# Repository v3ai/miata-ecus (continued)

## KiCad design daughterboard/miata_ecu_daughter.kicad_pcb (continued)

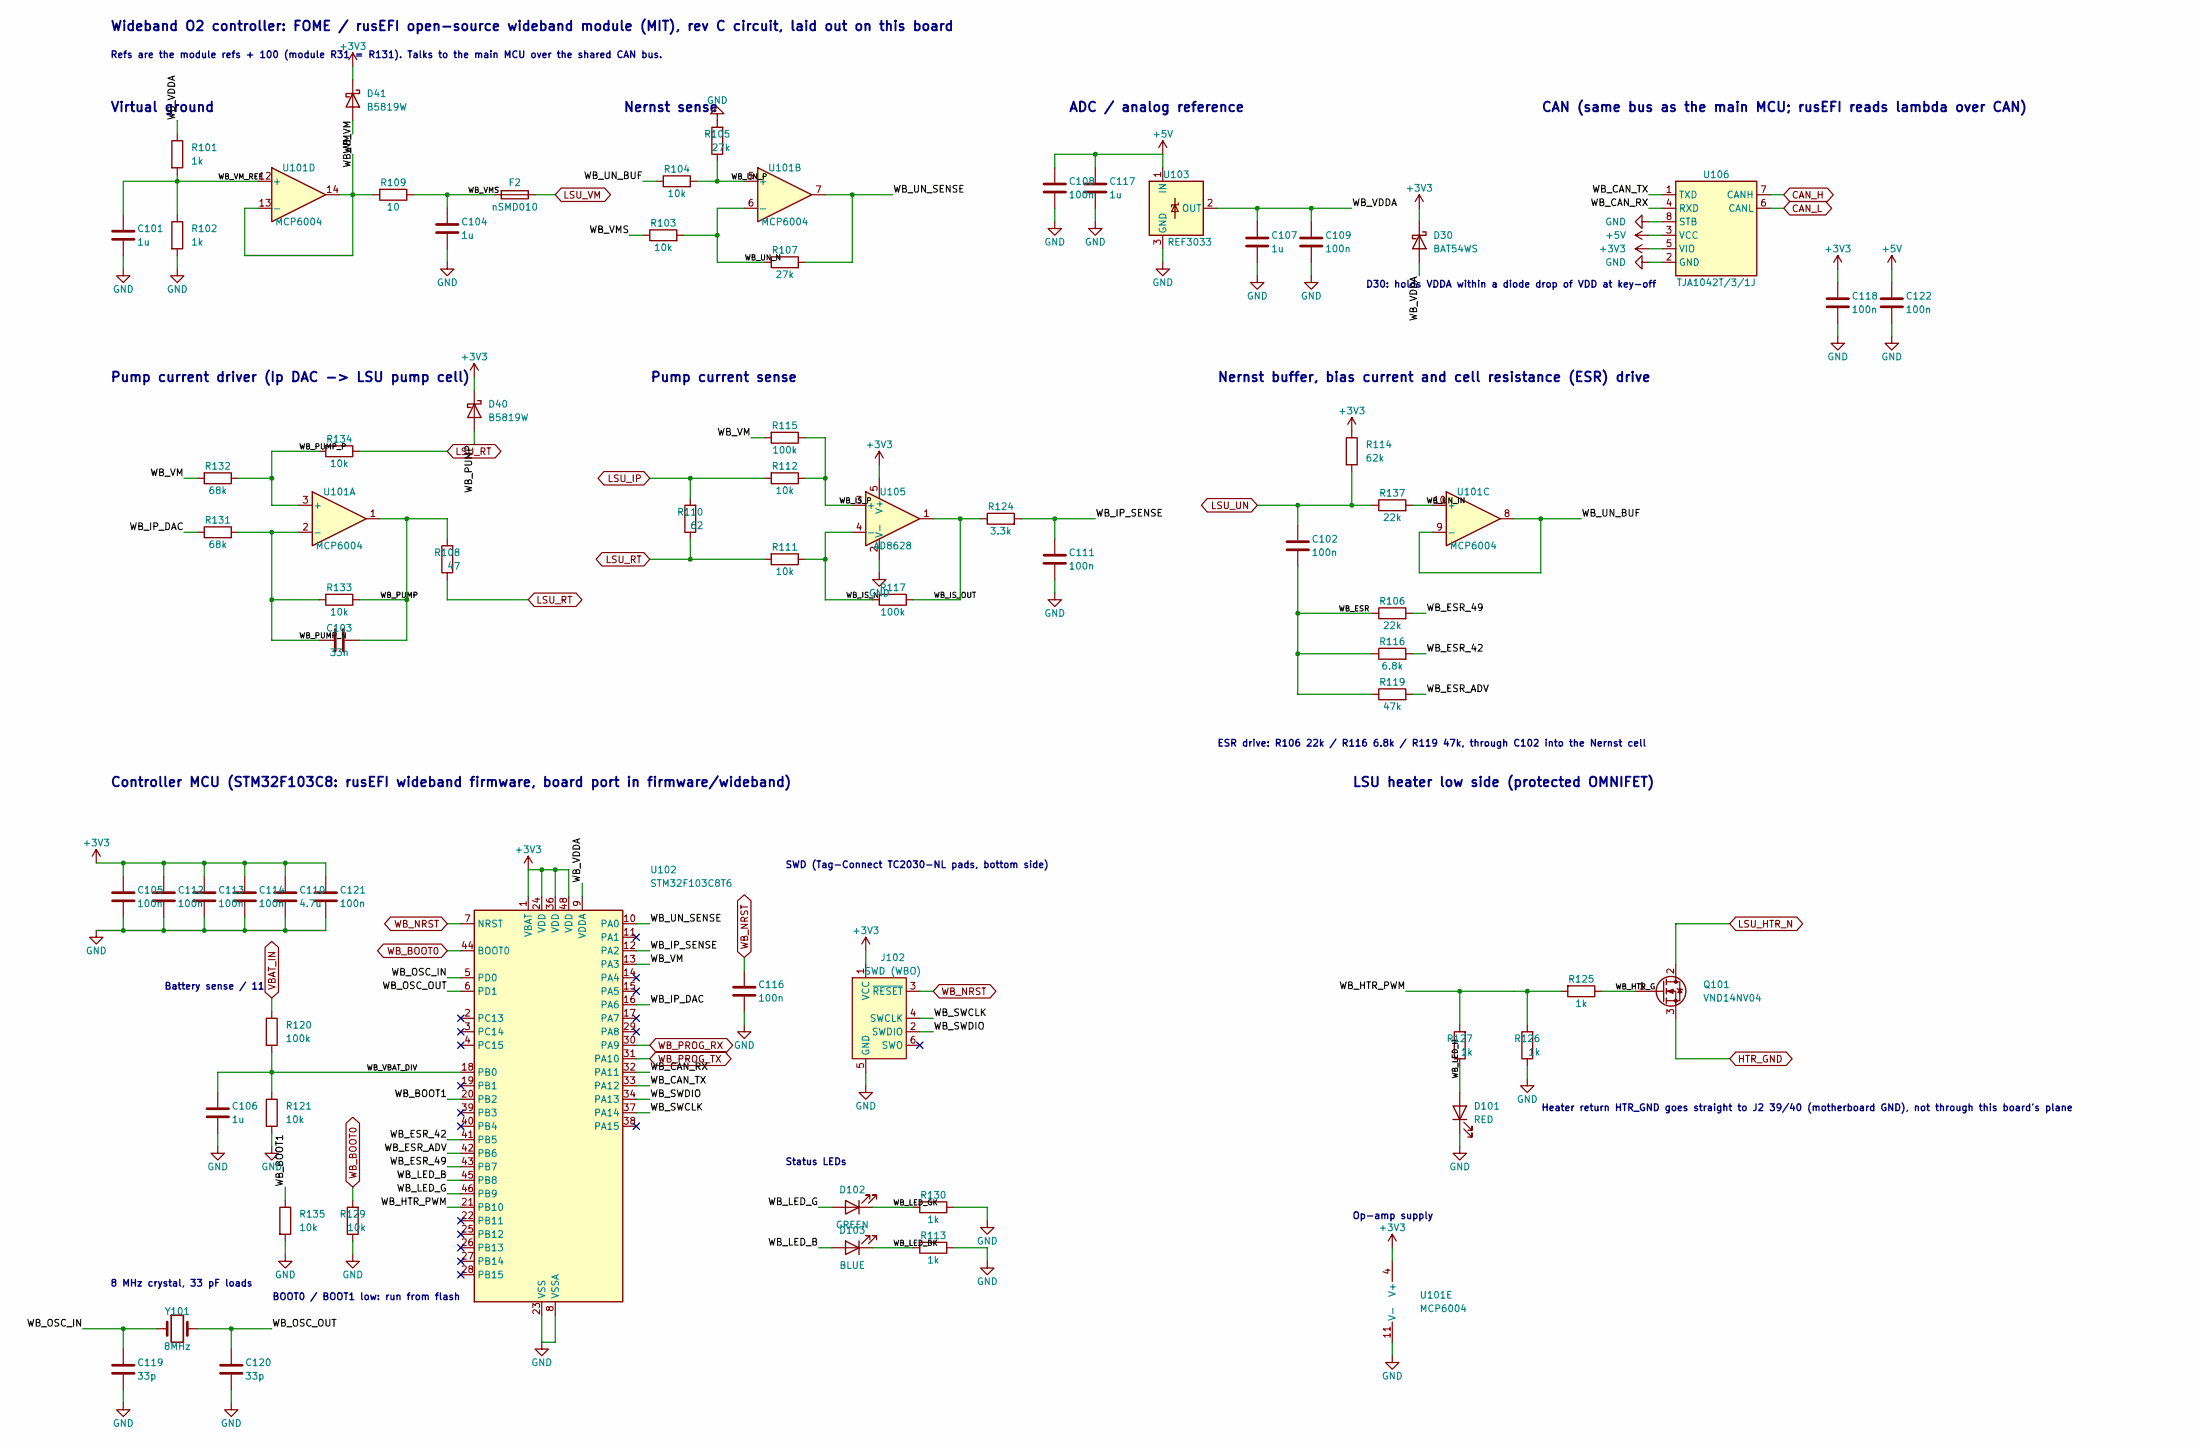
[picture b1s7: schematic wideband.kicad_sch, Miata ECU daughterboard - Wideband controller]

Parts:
C101, C104, C106, C107, C117: 1u; C_0402_1005Metric; LCSC C52923
C102, C105, C108, C109, C111, C112, C113, C114, C116, C118, C121, C122: 100n; C_0402_1005Metric; LCSC C1525
C103: 33n; C_0402_1005Metric; LCSC C106862
C110: 4.7u; C_0603_1608Metric; LCSC C19666
C119, C120: 33p; C_0402_1005Metric; LCSC C1562
D30: BAT54WS; D_SOD-323; LCSC C124205
D40, D41: B5819W; D_SOD-123; LCSC C8598
D101: RED; LED_0603_1608Metric; LCSC C2286
D102: GREEN; LED_0603_1608Metric; LCSC C12624
D103: BLUE; LED_0603_1608Metric; LCSC C2288
F2: nSMD010; Fuse_1206_3216Metric; LCSC C70065
J102: SWD (WBO); Tag-Connect_TC2030-IDC-NL_2x03_P1.27mm_Vertical
Q101: VND14NV04; TO-252-2; LCSC C2649436
R101, R102, R113, R125, R126, R127, R130: 1k; R_0402_1005Metric; LCSC C11702
R103, R104, R111, R112, R121, R129, R133, R134, R135: 10k; R_0402_1005Metric; LCSC C25744
R105, R107: 27k; R_0402_1005Metric; LCSC C25771
R106, R137: 22k; R_0402_1005Metric; LCSC C25768
R108: 47; R_1206_3216Metric; LCSC C17969
R109: 10; R_1206_3216Metric; LCSC C17903
R110: 62; R_1206_3216Metric; LCSC C17971
R114: 62k; R_0603_1608Metric; LCSC C23221
R115, R117, R120: 100k; R_0402_1005Metric; LCSC C25741
R116: 6.8k; R_0402_1005Metric; LCSC C25917
R119: 47k; R_0402_1005Metric; LCSC C25792
R124: 3.3k; R_0402_1005Metric; LCSC C25890
R131, R132: 68k; R_0402_1005Metric; LCSC C36871
U101: MCP6004; TSSOP-14_4.4x5mm_P0.65mm; LCSC C50282
U102: STM32F103C8T6; LQFP-48_7x7mm_P0.5mm; LCSC C8734
U103: REF3033; SOT-23; LCSC C36658
U105: AD8628; SOT-23-5; LCSC C29309
U106: TJA1042T/3/1J; SOIC-8_3.9x4.9mm_P1.27mm; LCSC C132227
Y101: 8MHz; Crystal_SMD_5032-2Pin_5.0x3.2mm; LCSC C115962

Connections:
+3V3: C105.1, C110.1, C112.1, C113.1, C114.1, C118.1, C121.1, D30.1 (K), D40.1 (K), D41.1 (K), J102.1 (VCC), R114.1, U101.4 (V+), U102.1 (VBAT), U102.24 (VDD), U102.36 (VDD), U102.48 (VDD), U105.5 (V+), U106.5 (VIO); also elsewhere on the board
+5V: C108.1, C117.1, C122.1, U103.1 (IN), U106.3 (VCC); also elsewhere on the board
/Wideband controller/WB_BOOT1: R135.1, U102.20 (PB2)
/Wideband controller/WB_CAN_RX: U102.32 (PA11), U106.4 (RXD)
/Wideband controller/WB_CAN_TX: U102.33 (PA12), U106.1 (TXD)
/Wideband controller/WB_ESR: C102.2, R106.1, R116.1, R119.1
/Wideband controller/WB_ESR_42: R116.2, U102.41 (PB5)
/Wideband controller/WB_ESR_49: R106.2, U102.43 (PB7)
/Wideband controller/WB_ESR_ADV: R119.2, U102.42 (PB6)
/Wideband controller/WB_HTR_G: Q101.1 (G), R125.1
/Wideband controller/WB_HTR_PWM: R125.2, R126.2, R127.2, U102.21 (PB10)
/Wideband controller/WB_IP_DAC: R131.1, U102.16 (PA6)
/Wideband controller/WB_IP_SENSE: C111.1, R124.2, U102.12 (PA2)
/Wideband controller/WB_IS_N: R111.1, R117.2, U105.4 (-)
/Wideband controller/WB_IS_OUT: R117.1, R124.1, U105.1
/Wideband controller/WB_IS_P: R112.1, R115.1, U105.3 (+)
/Wideband controller/WB_LED_B: D103.2 (A), U102.45 (PB8)
/Wideband controller/WB_LED_BK: D103.1 (K), R113.2
/Wideband controller/WB_LED_G: D102.2 (A), U102.46 (PB9)
/Wideband controller/WB_LED_GK: D102.1 (K), R130.2
/Wideband controller/WB_LED_H: D101.2 (A), R127.1
/Wideband controller/WB_OSC_IN: C119.1, U102.5 (PD0), Y101.1
/Wideband controller/WB_OSC_OUT: C120.1, U102.6 (PD1), Y101.2
/Wideband controller/WB_PUMP: C103.1, D40.2 (A), R108.2, R133.1, U101.1
/Wideband controller/WB_PUMP_N: C103.2, R131.2, R133.2, U101.2 (-)
/Wideband controller/WB_PUMP_P: R132.1, R134.2, U101.3 (+)
/Wideband controller/WB_SWCLK: J102.4 (SWCLK), U102.37 (PA14)
/Wideband controller/WB_SWDIO: J102.2 (SWDIO), U102.34 (PA13)
/Wideband controller/WB_UN_BUF: R104.1, U101.8, U101.9 (-)
/Wideband controller/WB_UN_IN: R137.2, U101.10 (+)
/Wideband controller/WB_UN_N: R103.2, R107.1, U101.6 (-)
/Wideband controller/WB_UN_P: R104.2, R105.1, U101.5 (+)
/Wideband controller/WB_UN_SENSE: R107.2, U101.7, U102.10 (PA0)
/Wideband controller/WB_VBAT_DIV: C106.1, R120.2, R121.1, U102.18 (PB0)
/Wideband controller/WB_VDDA: C107.1, C109.1, D30.2 (A), R101.1, U102.9 (VDDA), U103.2 (OUT)
/Wideband controller/WB_VM: D41.2 (A), R109.2, R115.2, R132.2, U101.13 (-), U101.14, U102.13 (PA3)
/Wideband controller/WB_VMS: C104.1, F2.2, R103.1, R109.1
/Wideband controller/WB_VM_REF: C101.1, R101.2, R102.1, U101.12 (+)
CAN_H: U106.7 (CANH); also elsewhere on the board
CAN_L: U106.6 (CANL); also elsewhere on the board
GND: C101.2, C104.2, C105.2, C106.2, C107.2, C108.2, C109.2, C110.2, C111.2, C112.2, C113.2, C114.2, C116.2, C117.2, C118.2, C119.2, C120.2, C121.2, C122.2, D101.1 (K), J102.5 (GND), R102.2, R105.2, R113.1, R121.2, R126.1, R129.1, R130.1, R135.2, U101.11 (V-), U102.8 (VSSA), U102.23 (VSS), U102.35 (VSS), U102.47 (VSS), U103.3 (GND), U105.2 (V-), U106.2 (GND), U106.8 (STB); also elsewhere on the board
HTR_GND: Q101.3 (S); also elsewhere on the board
LSU_HTR_N: Q101.2 (D); also elsewhere on the board
LSU_IP: R110.2, R112.2; also elsewhere on the board
LSU_RT: R108.1, R110.1, R111.2, R134.1; also elsewhere on the board
LSU_UN: C102.1, R114.2, R137.1; also elsewhere on the board
LSU_VM: F2.1; also elsewhere on the board
VBAT_IN: R120.1; also elsewhere on the board
WB_BOOT0: R129.2, U102.44 (BOOT0); also elsewhere on the board
WB_NRST: C116.1, J102.3 (~RESET), U102.7 (NRST); also elsewhere on the board
WB_PROG_RX: U102.30 (PA9); also elsewhere on the board
WB_PROG_TX: U102.31 (PA10); also elsewhere on the board

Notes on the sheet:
Wideband O2 controller: FOME / rusEFI open-source wideband module (MIT), rev C circuit, laid out on this board
Refs are the module refs + 100 (module R31 = R131). Talks to the main MCU over the shared CAN bus.
Virtual ground
Nernst sense
ADC / analog reference
D30: holds VDDA within a diode drop of VDD at key-off
CAN (same bus as the main MCU; rusEFI reads lambda over CAN)
Pump current driver (Ip DAC -> LSU pump cell)
Pump current sense
Nernst buffer, bias current and cell resistance (ESR) drive
ESR drive: R106 22k / R116 6.8k / R119 47k, through C102 into the Nernst cell
Controller MCU (STM32F103C8: rusEFI wideband firmware, board port in firmware/wideband)
BOOT0 / BOOT1 low: run from flash
Battery sense / 11
8 MHz crystal, 33 pF loads
Status LEDs
SWD (Tag-Connect TC2030-NL pads, bottom side)
LSU heater low side (protected OMNIFET)
Heater return HTR_GND goes straight to J2 39/40 (motherboard GND), not through this board's plane
Op-amp supply

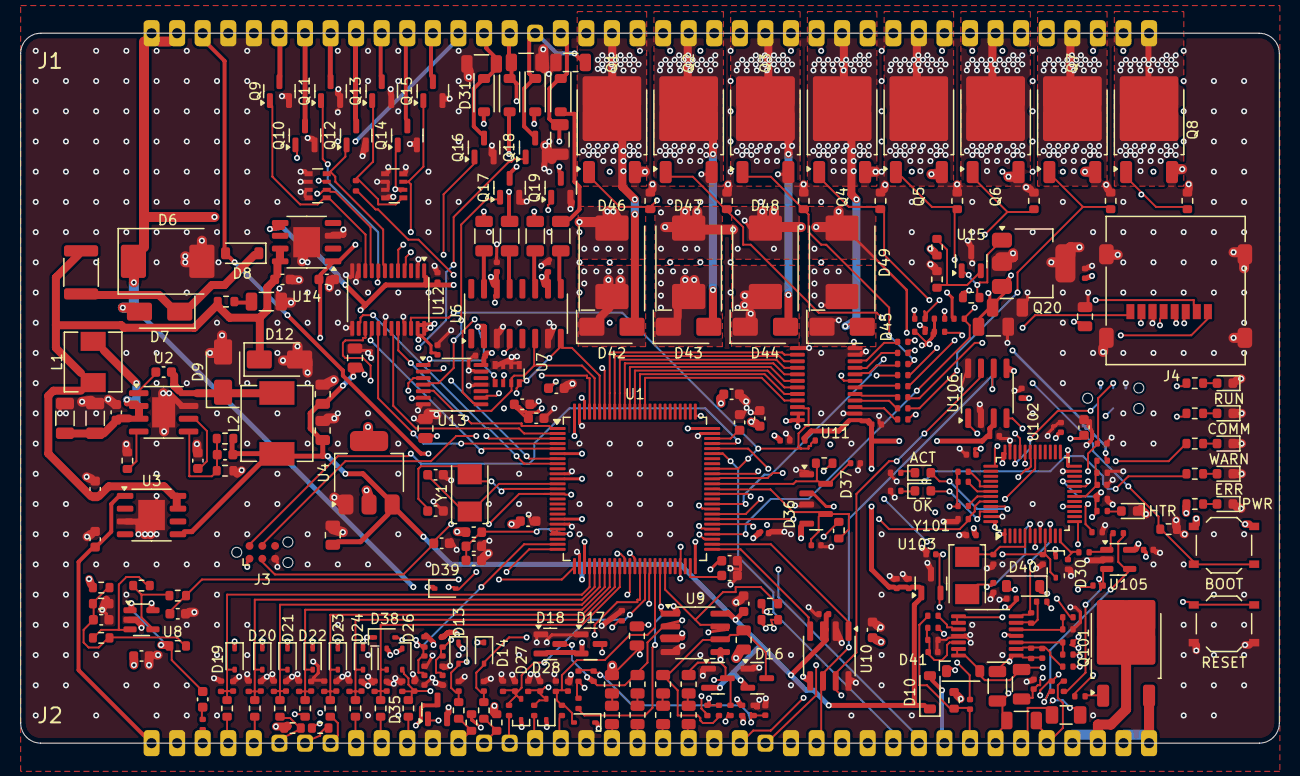
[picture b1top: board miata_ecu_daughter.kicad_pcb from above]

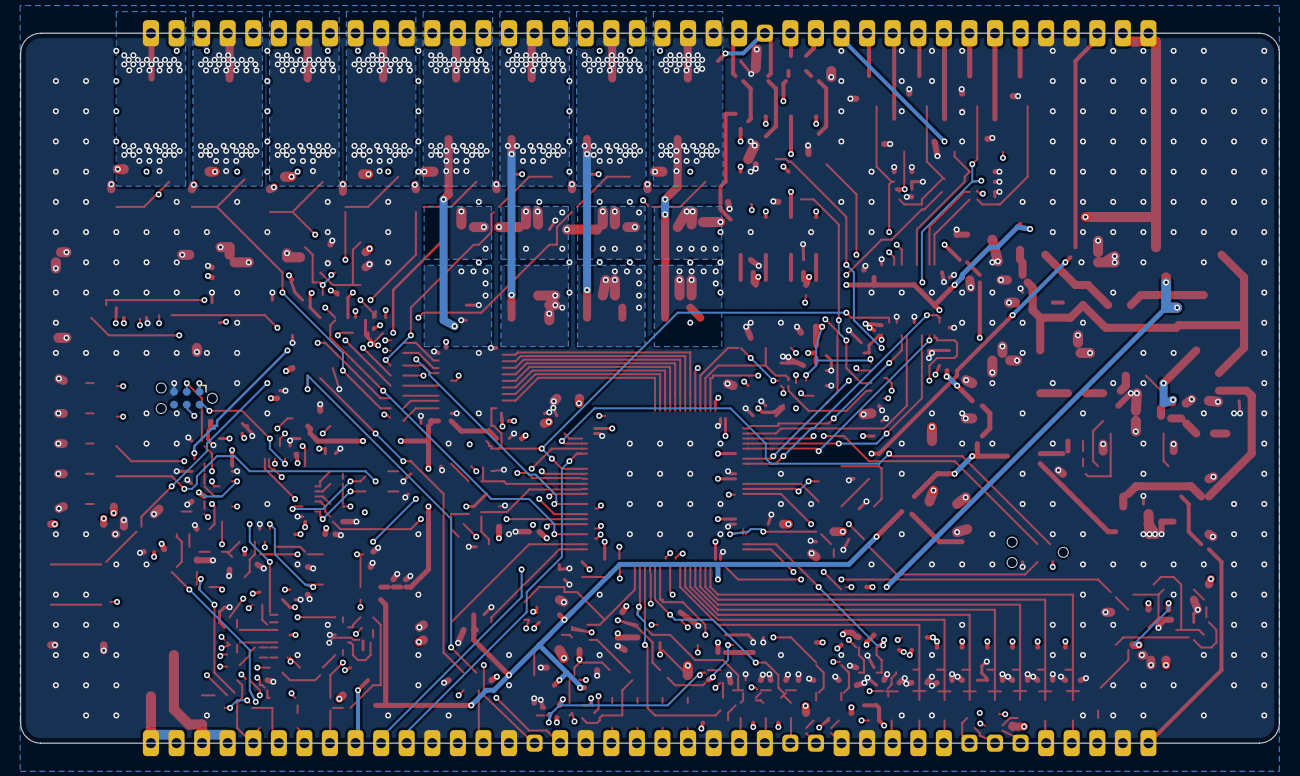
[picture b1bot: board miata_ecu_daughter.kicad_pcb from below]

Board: 6 copper layers, 125.0 x 70.5 mm, 334 parts (3 on the bottom side), 230 nets.

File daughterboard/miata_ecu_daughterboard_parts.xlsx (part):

Group | Qty | Value | Description | Designators | Footprint | LCSC # | JLC type | Notes | Manufacturer | MPN
MCU & support
MCU & support | 7 | 100n |  | C1, C2, C3, C5, C6, C12, C15 | C_0603_1608Metric | C14663 | Basic |  | YAGEO | CC0603KRX7R9BB104
MCU & support | 1 | 100n |  | C4 | C_0402_1005Metric | C1525 | Basic |  | Samsung Electro-Mechanics | CL05B104KO5NNNC
MCU & support | 1 | 10k |  | R1 | R_0603_1608Metric | C25804 | Basic |  | UNI-ROYAL(Uniroyal Elec) | 0603WAF1002T5E
MCU & support | 1 | 1u |  | C11 | C_0603_1608Metric | C15849 | Basic |  | Samsung Electro-Mechanics | CL10A105KB8NNNC
MCU & support | 2 | 2.2u |  | C9, C10 | C_0603_1608Metric | C23630 | Basic |  | Samsung Electro-Mechanics | CL10A225KO8NNNC
MCU & support | 2 | 33p |  | C13, C14 | C_0603_1608Metric | C1663 | Extended |  | Samsung Electro-Mechanics | CL10C330JB8NNNC
MCU & support | 2 | 4.7u |  | C7, C8 | C_0603_1608Metric | C19666 | Basic |  | Samsung Electro-Mechanics | CL10A475KO8NNNC
MCU & support | 1 | 8MHz | 8MHz crystal 5032, 20pF (YXC X50328MSB2GI) | Y1 | Crystal_SMD_5032-2Pin_5.0x3.2mm | C115962 | Extended |  | YXC Crystal Oscillators | X50328MSB2GI
MCU & support | 1 | BLM18PG221 |  | FB1 | L_0603_1608Metric | C80165 | Extended |  | Murata | BLM18PG221SN1D
MCU & support | 1 | BOOT |  | SW1 | SW_Push_1P1T_XKB_TS-1187A | C318884 | Basic |  | XKB Connection | TS-1187A-B-A-B
MCU & support | 1 | RESET |  | SW2 | SW_Push_1P1T_XKB_TS-1187A | C318884 | Basic |  | XKB Connection | TS-1187A-B-A-B
MCU & support | 1 | STM32F405VGT6 | MCU, Cortex-M4F 168MHz, 1MB flash, LQFP-100 | U1 | LQFP-100_14x14mm_P0.5mm | C56621 | Extended |  | STMicroelectronics | STM32F405VGT6
MCU & support | 1 | SWD | Tag-Connect TC2030-NL footprint, nothing to place | J3 | Tag-Connect_TC2030-IDC-NL_2x03_P1.27mm_Vertical |  |  | Not assembled
Status LEDs
Status LEDs | 5 | 1k |  | R2, R3, R4, R5, R6 | R_0603_1608Metric | C21190 | Basic |  | UNI-ROYAL(Uniroyal Elec) | 0603WAF1001T5E
Status LEDs | 1 | BLUE |  | D2 | LED_0603_1608Metric | C2288 | Extended |  | Hubei KENTO Elec | KT-0603B
Status LEDs | 2 | GREEN |  | D1, D5 | LED_0603_1608Metric | C12624 | Extended |  | Hubei KENTO Elec | KT-0603G
Status LEDs | 1 | RED |  | D4 | LED_0603_1608Metric | C2286 | Basic |  | Hubei KENTO Elec | KT-0603R
Status LEDs | 1 | YELLOW |  | D3 | LED_0603_1608Metric | C2287 | Extended |  | Hubei KENTO Elec | KT-0603Y
Power
Power | 1 | 1 |  | R7 | R_0603_1608Metric | C22936 | Basic |  | UNI-ROYAL(Uniroyal Elec) | 0603WAF100KT5E
Power | 1 | 100n |  | C19 | C_0603_1608Metric | C14663 | Basic |  | YAGEO | CC0603KRX7R9BB104
Power | 2 | 100n |  | C28, C29 | C_0402_1005Metric | C1525 | Basic |  | Samsung Electro-Mechanics | CL05B104KO5NNNC
Power | 1 | 10k |  | R8 | R_0603_1608Metric | C25804 | Basic |  | UNI-ROYAL(Uniroyal Elec) | 0603WAF1002T5E
Power | 1 | 10n |  | C20 | C_0603_1608Metric | C57112 | Basic |  | FH(Guangdong Fenghua Advanced Tech) | 0603B103K500NT
Power | 4 | 10u |  | C22, C23, C26, C27 | C_0805_2012Metric | C15850 | Basic |  | Samsung Electro-Mechanics | CL21A106KAYNNNE
Power | 3 | 10u/50V |  | C16, C17, C18 | C_1206_3216Metric | C13585 | Basic |  | Samsung Electro-Mechanics | CL31A106KBHNNNE
Power | 1 | 10uH |  | L2 | L_Sunlord_MWSA0603S | C132141 | Extended |  | Sunlord | MWSA0603S-100MT
Power | 1 | 12k |  | R10 | R_0603_1608Metric | C22790 | Basic |  | UNI-ROYAL(Uniroyal Elec) | 0603WAF1202T5E
Power | 2 | 1u |  | C24, C25 | C_0603_1608Metric | C15849 | Basic |  | Samsung Electro-Mechanics | CL10A105KB8NNNC
Power | 1 | 2.2uH |  | L1 | L_Sunlord_MWSA0503S | C177247 | Extended |  | cjiang (Changjiang Microelectronics Tech) | FXL0530-2R2-M
Power | 1 | 220p |  | C21 | C_0603_1608Metric | C1603 | Basic |  | Samsung Electro-Mechanics | CL10B221KB8NNNC
Power | 2 | 33k |  | R11, R13 | R_0402_1005Metric | C25779 | Basic |  | UNI-ROYAL(Uniroyal Elec) | 0402WGF3302TCE
Power | 2 | 6.8k |  | R12, R14 | R_0402_1005Metric | C25917 | Basic |  | UNI-ROYAL(Uniroyal Elec) | 0402WGF6801TCE
Power | 1 | 68k |  | R9 | R_0603_1608Metric | C23231 | Basic |  | UNI-ROYAL(Uniroyal Elec) | 0603WAF6802T5E
Power | 1 | B360A | 3A 60V Schottky, buck catch diode | D9 | D_SMA | C94193 | Extended |  | Diodes Incorporated | B360A-13-F
Power | 2 | B5819W | 1A 40V Schottky | D8, D10 | D_SOD-123 | C8598 | Extended |  | JSCJ | B5819W SL
Power | 1 | LDL1117S33R |  | U4 | SOT-223-3_TabPin2 | C435835 | Extended |  | STMicroelectronics | LDL1117S33R
Power | 1 | LMR14020 | 40V 2A buck converter, 12V -> 5V | U2 | SOIC-8-1EP_3.9x4.9mm_P1.27mm_EP2.29x3mm | C187824 | Extended |  | Texas Instruments | LMR14020SDDAR
Power | 1 | SMCJ30A | 1500W TVS, load dump | D6 | D_SMC | C224048 | Extended |  | Littelfuse | SMCJ30A
Power | 1 | SS34 | 3A 40V Schottky | D7 | D_SMA | C8678 | Basic |  | MDD(Microdiode Semiconductor) | SS34
Power | 1 | TLS115B0EJ | 5V sensor supply tracker, short-to-battery protected | U3 | Infineon_PG-DSO-8-27_3.9x4.9mm_EP2.65x3mm | C3743696 | Extended |  | Infineon | TLS115B0EJ
Injector / solenoid drivers
Injector / solenoid drivers | 1 | BCP53-16 |  | Q20 | SOT-223 | C85085 | Extended |  | Nexperia | BCP53-16,115
Injector / solenoid drivers | 1 | VND14NV04 |  | Q101 | TO-252-2 | C2649436 | Extended |  | STMicroelectronics | VND14NV04TR-E
Injector / solenoid drivers | 8 | VND7NV04TR-E |  | Q1, Q2, Q3, Q4, Q5, Q6, Q7, Q8 | TO-252-2 | C155605 | Extended |  | ST | VND7NV04TR-E
Injector / solenoid drivers | 11 | ZXMS6004FFTA |  | Q9, Q10, Q11, Q12, Q13, Q14, Q15, Q16, Q17, Q18, Q19 | SOT-23 | C95063 | Extended |  | DIODES | ZXMS6004FFTA
Ignition drivers
Ignition drivers | 4 | 100 |  | R15, R16, R17, R18 | R_1206_3216Metric | C17901 | Extended |  | UNI-ROYAL | 1206W4F1000T5E
Ignition drivers | 2 | 1u |  | C34, C35 | C_0402_1005Metric | C52923 | Extended |  | Samsung Electro-Mechanics | CL05A105KA5NQNC
Ignition drivers | 4 | 3.3k |  | R144, R145, R146, R147 | R_1206_3216Metric | C26032 | Extended |  | UNI-ROYAL | 1206W4F3301T5E
Ignition drivers | 1 | 4x10k |  | RN1 | R_Array_Convex_4x0603 | C29718 | Basic |  | UNI-ROYAL(Uniroyal Elec) | 4D03WGJ0103T5E
Ignition drivers | 1 | 74HCT04PW |  | U13 | TSSOP-14_4.4x5mm_P0.65mm | C131317 | Extended |  | Nexperia | 74HCT04PW,118
Ignition drivers | 4 | B5819W | 1A 40V Schottky | D31, D32, D33, D34 | D_SOD-123 | C8598 | Extended |  | JSCJ | B5819W SL
Ignition drivers | 1 | BAT54WS |  | D39 | D_SOD-323 | C124205 | Extended |  | Diodes Incorporated | BAT54WS-7-F
Ignition drivers | 1 | Mezz_Power_Out | 1x40 2.54mm male header (power/outputs) | J1 | Castellated_1x40_P2.54mm |  |  | Not assembled
Ignition drivers | 2 | TC4427 | Dual 1.5A driver, 5V logic out for COP smart coils | U6, U7 | SOIC-8_3.9x4.9mm_P1.27mm | C20551 | Extended |  | Microchip | TC4427AEOA713
Knock input
Knock input | 3 | 100k |  | R45, R46, R47 | R_0603_1608Metric | C25803 | Basic |  | UNI-ROYAL(Uniroyal Elec) | 0603WAF1003T5E
Knock input | 1 | 100n |  | C44 | C_0603_1608Metric | C14663 | Basic |  | YAGEO | CC0603KRX7R9BB104
Knock input | 1 | 10k |  | R49 | R_0603_1608Metric | C25804 | Basic |  | UNI-ROYAL(Uniroyal Elec) | 0603WAF1002T5E
Knock input | 1 | 10n |  | C46 | C_0603_1608Metric | C57112 | Basic |  | FH(Guangdong Fenghua Advanced Tech) | 0603B103K500NT
Knock input | 1 | 1u |  | C45 | C_0603_1608Metric | C15849 | Basic |  | Samsung Electro-Mechanics | CL10A105KB8NNNC
Knock input | 1 | 2.2k |  | R138 | R_0402_1005Metric | C25879 | Basic |  | UNI-ROYAL | 0402WGF2201TCE
Knock input | 1 | 330 |  | R50 | R_0603_1608Metric | C23138 | Basic |  | UNI-ROYAL(Uniroyal Elec) | 0603WAF3300T5E
Knock input | 1 | 47k |  | R48 | R_0603_1608Metric | C25819 | Basic |  | UNI-ROYAL(Uniroyal Elec) | 0603WAF4702T5E
Knock input | 1 | LMV321IDBVR | Op-amp, knock sensor gain stage | U8 | SOT-23-5 | C7972 | Extended |  | Texas Instruments | LMV321IDBVR
VR (crank/cam) input
VR (crank/cam) input | 4 | 100k |  | R73, R74, R75, R76 | R_0402_1005Metric | C25741 | Extended |  | UNI-ROYAL(Uniroyal Elec) | 0402WGF1003TCE
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
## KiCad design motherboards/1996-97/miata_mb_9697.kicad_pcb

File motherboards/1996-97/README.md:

# Miata ECU motherboard 1996-1997 (NA8 OBD2), rev 0.15

The motherboard replaces the stock Mazda ECU board inside the **stock ECU case**. It carries:

- the stock harness header;
- the year-independent I/O: the wideband sensor connector (AEM X-Series harness), USB-C, the MAP sensor and the add-on header (flex fuel, nitrous, CAN, boost);
- the lands for the universal daughterboard, which does all the engine control (including the wideband controller): a castellated module soldered flat onto JD1 / JD2.

## Changes in this revision
- Rev 0.15: R37, a not-fitted 2.2 kOhm 1206 tachometer pull-up from 12 V to the tach output (the output is an open-drain driver; fit it only if the car's wiring does not pull the tach wire up, quickstart); the tracks at its pads were joined again (scripts/mb_rev19.sh). Also: no silkscreen lies on a pad, on a part or on other silkscreen any more (scripts/silk_clean.py, which now runs at every change and fails the build on any overlap): references that sat under their part or on a pad moved beside it; the daughterboard's land rows are labelled JD1 / JD2 (they read J1 / J2, the names of the harness header and the wideband plug), and the DAUGHTERBOARD text the module covers is gone; the MAP sensor's hint is one line, "MPX5700AP marking up", beside the sensor instead of under its body. Same pinout.
- Rev 0.14: J5's pin names are on both sides of the header, each next to its own row: the odd pins' names above it (the row nearer the daughterboard), the even pins' below it, all outside the shroud, so they stay readable with the ribbon cable's plug fitted. Pin numbers 1 / 2 and 19 / 20 at the shroud's ends replace the pin-1 triangle. To make room, the flex-fuel input's pull-up R35 and the nitrous input's pull-down R36 moved to the free board left of J5, and the tracks round them and under the names were joined again, with no via under a name (scripts/j5_mb.sh); J5's reference moved below the pin numbers. Same parts, nets and pinout.
- Rev 0.13: the add-on header J5's pins are named on the silkscreen below the header, where they stay readable with the ribbon cable's plug fitted: the even pins (the row nearer the board edge) in the band next to the header, the odd pins below them (scripts/j5_labels.py). Five ground stitching vias under the names moved sideways and U4's reference moved to its right; same copper otherwise, same parts and pinout.
- Rev 0.12, for daughterboard rev 0.13, the castellated module: JD1 / JD2 are rows of 40 SMD lands (1.5 x 3.0 mm, 1.2 mm under the module and 1.8 mm beyond its edge) instead of 1x40 sockets, and the standoff holes HD1-HD4 are gone. The module is soldered flat to the lands, so nothing may sit under it: the freewheel diode D1 above JD1, the pull-ups R20-R22 below JD2. The tracks that met the sockets on the bottom copper now reach the lands through vias beside them. The copper near the lands and the moved parts is ripped and joined again at the board's own rules (scripts/castellate_mb.sh); the wideband heater's return (1.0 mm) takes a new way to JD2, and the board's smallest via is 0.5 mm (0.3 mm hole) where a 0.6 mm one does not fit. Same nets and pinout; the earlier, socketed daughterboards do not fit.
- Rev 0.11: R21 / R22 fitted (4.7 kΩ to 12 V, C23162): the A/C request and clutch switches close to ground, and the firmware reads them active low; the harness-header holes are 1.3 mm (were 1.1 mm; TE asks for 1.35 mm), same 1.8 mm pads. For daughterboard rev 0.12 (STM32F405, TJA1042 CAN transceivers); any daughterboard from rev 0.10 fits.
- Rev 0.10: no via in or against any SMD pad (they moved beside their pads); the air-temperature input reads the GM sensor that ships with every board, on the car's own wires.
- Rev 0.9: the wideband sensor connector J2 is now a JST PUD side-entry header (S08B-PUDSS-1, two rows of four at 2.0 mm) instead of rev 0.8's Molex Micro-Fit 2x4. AEM's instructions for the X-Series gauge name the harness's replacement terminal, JST SPUD-001T-P0.5, which is the contact of JST's PUD series (plug housing PUDP-08V-S): a Micro-Fit header would not have taken the plug. The wire colour of each pin is printed beside the connector, to check a harness against by eye. The board is routed again; nothing else changed.
- Rev 0.8, for daughterboard rev 0.10 (a rev 0.9 daughterboard fits too, without the new functions). The wideband sensor connector J2 is a Molex Micro-Fit 2x4 for the off-the-shelf AEM X-Series sensor harness (30-3427) instead of the 2x3 for a hand-made lead; that plug family was a guess, and wrong: corrected in rev 0.9. The separate air-temperature connector J3 and its jumper are gone: the stock sensor's harness wire goes straight to the air-temperature input. The add-on header J5 is a 2x10 box header for a ribbon cable and gains the flex-fuel input (4.7k pull-up to 5 V, R35), the nitrous arming input (10k pull-down, R36) and the CAN bus; a boost valve on it has its own freewheel diode (D5), and its +12 V fuse F4 holds 1.1 A instead of 0.5 A. Harness header TE 178780-1 as before.
- Rev 0.7, for daughterboard rev 0.9: the daughterboard sits 16 mm lower, centred on the board (42 mm from the top, as up to rev 0.7), with its J1 on its top edge again: JD1 and the upper standoffs HD1/HD2 are back at their rev 0.7 places, JD2, the lower standoffs HD3/HD4, the AUX header J5 (with F4 beside it) and the parts placed against JD2 (CAN termination R1/R6, pull-up options) are 16 mm lower, and the board is routed again. Not compatible with a rev 0.8 daughterboard.
- Rev 0.6, for daughterboard rev 0.8: the harness's sensor 5 V (3I) and the AUX header pin J5-14 now come from the daughterboard's protected 5 V (V5_EXT, JD1 pin 13, which was a ground pin): a sensor 5 V wire shorted to the battery no longer back-feeds the MAP sensor and the ECU's own 5 V. The MAP sensor keeps its own supply (V5_SENS). The daughterboard outline on the silkscreen is 16 mm taller (125 x 76 mm): its new strip of output drivers overhangs the free area above JD1.
- Rev 0.5: LSU heater fuse F1 is a 3 A hold PTC (LUTE 2920L300/30GR, 30 V, 2920 size) instead of the 2 A 1812 part. A cold LSU 4.9 heater draws 1.6-2.3 A rms at the start of the wideband's warm-up, more than the old fuse holds once warm, so it could trip and the controller time out. No 1812 PTC holds 3 A above 8 V.
- Rev 0.4: freewheel diode D1 on the idle valve to its +12 V feed (the PWM turn-off energy no longer goes into the daughterboard driver); F4 resettable fuse on the AUX +12 V pin J5-15; not-fitted 12 V pull-up options R20-R22 for the VSS / A/C / clutch inputs.
- Rev 0.3: IAT source is now a removable jumper (JP1, 1x3 2.54 mm header + shunt) instead of the R4 / R5 0R links: shunt on EXT (default) reads the IAT connector J3, on STOCK the stock harness sensor; labelled on the silkscreen.
- Rev 0.2: MAP sensor is now the MPX5700AP (absolute, case 867B, one barb; LCSC C90152) instead of the MPX5700DP: new footprint with the real lozenge body and offset barb, holes on the NXP 23.11 mm spacing with 3.3 mm M3 clearance drills.
- Rev 0.1: first release (design complete, case geometry provisional).

## Files
| Path | What |
|---|---|
| `miata_mb_9697.kicad_pro / .kicad_sch / .kicad_pcb` | KiCad 7 project. Root schematic plus three sheets: harness, daughterboard, I/O |
| `miata_mb_9697_schematic.pdf` | Schematic PDF |
| `fab/miata-ecu-motherboard-1996-97-rev0.15_jlcpcb_gerbers.zip`, `fab/miata-ecu-motherboard-1996-97-rev0.15_jlcpcb_bom.csv`, `fab/miata-ecu-motherboard-1996-97-rev0.15_jlcpcb_cpl.csv` | JLC fabrication and assembly files (2 layers, 1.6 mm). The JLC BOM is the SMD parts and USB-C only |
| `fab/miata-ecu-motherboard-1996-97-rev0.15_self_order_bom.csv` | Everything you order and fit yourself: harness header, through-hole connectors, MAP sensor, shunt and screws, plus the not-fitted options. Its columns load into LCSC's BOM tool |
| `fab/miata-ecu-motherboard-1996-97-rev0.15_parts_list.csv` | Every part, including the hand-fitted and not-fitted ones |
| `fab/drc_report.txt` | KiCad DRC |
| `ecu_mb.pretty/`, `fp-lib-table` | Project footprints (harness header, MAP sensor lying flat, USB-C, M4 case hole) |
| `renders/` | Top and bottom copper; `assembly.jpg` / `assembly_lifted.jpg`, the 3D render of this board with the daughterboard (`scripts/render_photos.py`) |
| `scripts/` | The design source; `mb_make.sh` rebuilds the whole board |

## Case fit
**PROVISIONAL.** No source gives this case's board outline and mounting holes yet (the open-source boards for these years either use their own enclosure or a different Mazda case). Until a stock board or case is measured, this board uses the NA case outline and holes as a stand-in, with the header centred on the top edge. Moving to the real outline is a change of OUTLINE / CASE_HOLES / HDR_1A in the year module plus an automatic reroute. **Order one pilot board and fit it in the stock case before ordering more** (ORDERING.md, "Order in this sequence"): the owner's own pilot of two 1996-97 sets is how that case gets measured.

Board: **154.0 × 161.5 mm**, 1.6 mm. The origin is the top-left corner and y points down, toward the bottom edge.

| Hole | x, y (mm) |
|---|---|
| H3 | 4.0, 84.0 |
| H4 | 150.0, 84.0 |
| H5 | 4.0, 143.0 |
| H6 | 150.0, 143.0 |

All holes are 4.5 mm plated with a 7 mm pad, tied to GND, for M4 screws. Harness header terminal 1A sits at (16.00, 18.13) mm (lower pin row).

## Harness header
TE **178780-1**, 76 positions (alternates 174915-6, 3-178780-6): OEM plug 1 = 1A-1V (22), plug 2 = 2A-2L (12, no harness plug: left open), plug 3 = 3A-3P (16), plug 4 = 4A-4Z (26). Hellen's board names the same cavities 1 / 4 / 2 / 3. Fitted by hand.

| Pin | Net | Use | Stock function / note |
|---|---|---|---|
| 1A | `OUT_FAN` | fan relay | cooling (radiator) fan relay |
| 1B | `OUT_LS7` | spare low side | fan No.2 / A/C condenser fan relay |
| 1E | `OUT_CEL` | check engine lamp | MIL |
| 1G | `OUT_AC` | A/C relay | A/C relay |
| 1K | `IN_SW2` | 12 V switch input 2 | A/C switch / refrigerant pressure switch |
| 1L | `IN_SW3` | 12 V switch input 3 | clutch switch |
| 1M | `IN_SW1` | 12 V switch input 1 | vehicle speed sensor |
| 1O | `GND` | ground | ground |
| 1U | `OUT_FP` | fuel pump relay | fuel pump relay |
| 3B | `IN_AUX3` | spare analog 3 | MAF signal |
| 3C | `IN_AUX2` | spare analog 2 | front HO2S (narrowband) |
| 3D | `IN_AUX1` | spare analog 1 | rear HO2S |
| 3F | `IN_TPS` | TPS | throttle position sensor |
| 3G | `IN_CLT` | coolant temp | coolant temperature sensor |
| 3I | `V5_EXT` | sensor 5 V reference (out; protected, short-to-battery proof) | +5 V sensor reference (TPS, MAF) |
| 3K | `IN_IAT` | air temperature (the stock sensor) | intake air temperature sensor (in the airflow meter) |
| 3M | `OUT_VVT` | PWM low side (VVT driver) | front HO2S heater (PWM low side; no VVT on this engine) |
| 3O | `GND` | ground | sensor ground (BLK/BLU) |
| 4A | `GND` | ground | ground |
| 4B | `VBAT_IN` | ECU power (main relay) | ECU +12 V from the main relay (WHT/RED) |
| 4C | `GND` | ground |  |
| 4D | `GND` | ground |  |
| 4F | `IN_HALL1` | hall input 1 (crank) | CAS 4-pulse crank angle (SGT), hall / open collector |
| 4G | `IN_HALL2` | hall input 2 (cam) | CAS 2-pulse cam (SGC), hall / open collector |
| 4L | `OUT_TACH` | tach out | tachometer |
| 4N | `OUT_IGN1` | ignition 1 (5 V logic) | igniter cylinders 1 & 4 |
| 4Q | `OUT_IACV` | idle air valve | idle air control valve (low side) |
| 4R | `OUT_IGN2` | ignition 2 (5 V logic) | igniter cylinders 2 & 3 |
| 4U | `OUT_INJ1` | injector 1 |  |
| 4V | `OUT_INJ2` | injector 2 |  |
| 4W | `OUT_INJ3` | injector 3 |  |
| 4X | `OUT_INJ4` | injector 4 |  |

Not connected: 1C, 1D, 1F, 1H, 1I, 1J, 1N, 1P, 1Q, 1R, 1S, 1T, 1V, 2A, 2B, 2C, 2D, 2E, 2F, 2G, 2H, 2I, 2J, 2K, 2L, 3A, 3E, 3H, 3J, 3L, 3N, 3P, 4E, 4H, 4I, 4J, 4K, 4M, 4O, 4P, 4S, 4T, 4Y, 4Z.

## Bottom edge, left to right
| Ref | What | Notes |
|---|---|---|
| J2 | Wideband sensor (JST PUD side-entry header S08B-PUDSS-1, 2×4, 2.0 mm) | For the **AEM X-Series sensor harness 30-3427** and a Bosch LSU 4.9. Pin 1 trim (LSU RT, green wire), 2 heater − (white), 3 common (VM, orange), 5 pump current (IP, red), 6 sense (UN, black), 8 heater + (brown); 4 and 7 empty. Pins 1/2 are the first column, odd pins in the row away from the board edge; the colours are printed beside the connector. The pin functions and the terminal (JST SPUD-001T-P0.5, the PUD series' contact) are from AEM's instructions for the gauge; **nobody has plugged a harness into this board yet: compare the wire colours with the print before the first use.** Heater fed from the main relay through F1 (3 A hold, 30 V, 2920). The controller is on the daughterboard |
| J4 | USB-C | USB 2.0 device: tuning, logging, DFU |
| U2 | MPX5700AP | Absolute MAP sensor (15-700 kPa, case 867B). Lies flat on 2 × M3, marking side up, leads bent 90° down, the single barb toward the board centre |

**Air temperature:** the car's own sensor's harness wire goes straight to the air temperature input, and the firmware is set for the stock Mazda sensor's curve: on 1989-97 the sensor is inside the airflow meter, so the meter stays plugged in; on 1999-2005 it is the separate sensor in the air filter box. A GM open-element sensor on the same wires is the option for a car whose airflow meter comes out ([INSTALL.md](../../INSTALL.md#7-air-temperature)). The pull-up is 2.7 kΩ.

**CAN:** R1 + R6 terminate the bus at the ECU end; remove R6 if the bus is terminated elsewhere. The bus is on the add-on header (J5-19 CAN H, J5-20 CAN L) for a dash or gauges; it is the bus the on-board wideband controller reports on, at 500 kbit/s.

**Add-on header (J5, 2×10 box header, 2.54 mm; a 20-way ribbon cable fits):** what the stock harness has no pins for.

| Pin | Net | Use |
|---|---|---|
| 1 | `OUT_IGN3` | ignition 3 (5 V logic), coil-on-plug |
| 2 | `OUT_IGN4` | ignition 4 (5 V logic), coil-on-plug |
| 3 | `OUT_BOOST` | boost valve, low side (freewheel diode D5 to pin 15 on the board) |
| 4 | `OUT_ALT` | alternator driver, low side |
| 5 | `OUT_MAINRLY` | main relay driver, low side |
| 6 | `IN_KNOCK` | knock sensor |
| 7 | `VR1_P` | VR input 1 + |
| 8 | `VR1_N` | VR input 1 − |
| 9 | `VR2_P` | VR input 2 + |
| 10 | `VR2_N` | VR input 2 − |
| 11 | `IN_AFR` | external 0-5 V wideband |
| 12 | `IN_FLEX` | flex-fuel sensor signal (4.7 kΩ pull-up to 5 V on the board, R35) |
| 13 | `IN_N2O` | nitrous arming switch: 12 V = armed (10 kΩ pull-down on the board, R36) |
| 14 | `V5_EXT` | sensor 5 V (protected) |
| 15 | `AUX_VBAT` | +12 V from the main relay through F4 (1.1 A hold) |
| 16 | `GND` | ground |
| 17 | `GND` | ground |
| 18 | `GND` | ground |
| 19 | `CAN_H` | CAN high |
| 20 | `CAN_L` | CAN low |

**Flex fuel** (GM / Continental type sensor): signal to J5-12, sensor +12 V from J5-15, ground to J5-16. In TunerStudio set the flex sensor input to "Flex input (J2-24)" (J2-24 is the daughterboard module's own pin name; on this board it is J5-12). **Nitrous:** arming switch from +12 V to J5-13; in TunerStudio enable nitrous control, set the trigger to "Nitrous arm (J2-25)" (J5-13 here) and pick a spare output (boost on J5-3, or the second fan output) for the solenoid relay. **Boost valve:** between J5-15 (+12 V) and J5-3. All of these need a rev 0.10 or later daughterboard.

**Protection:** D1 (and D2 where the VVT driver runs a coil) freewheel the PWM valve coils into their own +12 V feed, and D5 does the same for a boost valve on the add-on header, so the drivers don't absorb the turn-off energy. F4 fuses the add-on header's +12 V pin (1.1 A hold: a boost valve draws about 0.5 A).

**Switch inputs (R20-R22):** the A/C request and clutch switches close to ground (the stock ECU's tables: B+ open, under 2.5 V closed), so R21 and R22 pull them up to 12 V and the firmware reads both active low (fitted from rev 0.12; on an earlier board fit them by hand, 4.7 kΩ 0603). R20, the vehicle speed pull-up, is not fitted: fit it only if your car's speed signal switches to ground or is open collector.

**Sensor 5 V:** the harness's 5 V reference and the AUX header pin J5-14 come from the daughterboard's protected 5 V regulator (V5_EXT; it survives a short to the battery or to ground). The MAP sensor has its own supply (V5_SENS), so a damaged sensor wire doesn't take the MAP reading with it.

## Assembly
- The daughterboard (rev 0.13 on) is a castellated module: it lies flat on the board and its 80 edge half-holes are soldered to the lands JD1 / JD2, by reflow or with an iron ([INSTALL.md](../../INSTALL.md#soldering-the-daughterboard-to-the-motherboard)). Solder it on before the harness header, so the lands are easy to reach.
- Fitted by hand (all in `fab/miata-ecu-motherboard-1996-97-rev0.15_self_order_bom.csv`): the harness header (new: TE 178780-1, LCSC C5166246, few in stock; or salvage one from a stock ECU), the wideband sensor connector, the add-on header, any jumper headers and their shunts, the MAP sensor, and any not-fitted option links. JLCPCB fits only the SMD parts and USB-C. USB-C has through-hole shell pegs: check in JLC's quote whether that needs Standard PCBA.
- The case needs cut-outs in its bottom edge for the wideband connector, USB-C and the MAP hose, and a way out for the add-on ribbon cable.

## Still to verify
- **The case outline, mounting holes and header position (provisional here).**
- The 76-position header housing is 130 mm wide and reaches into the top-corner notches of the provisional (NA) outline; the real 1996-97 case must clear it.
- 4E / 4H: the separate OBD-II crank-pulley sensor (VR) is left unconnected, as on every PnP board found; rusEFI uses the CAS signals on 4F / 4G.
- 1O and 4A are tied to ground (sources agree they are grounds; power vs signal role unconfirmed).
- 4I (possible battery backup), 4K, 1D, 1H, 1I, 1P, 3H, 3J, 3N, 3P and the other unidentified cavities are left open.
- Brake switch (1Q) is not read: the spare inputs are 0-5 V analog, not 12 V switch inputs.

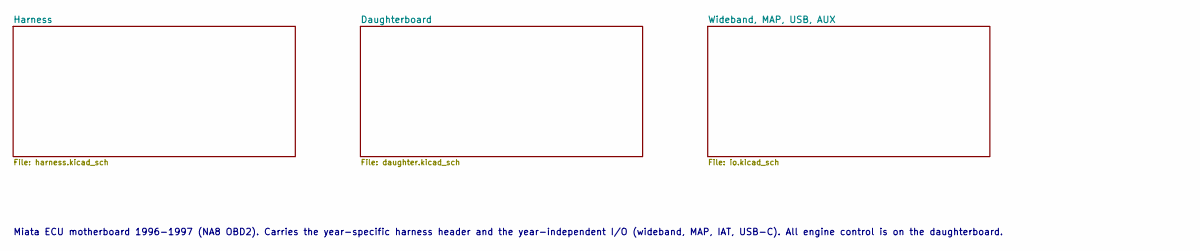
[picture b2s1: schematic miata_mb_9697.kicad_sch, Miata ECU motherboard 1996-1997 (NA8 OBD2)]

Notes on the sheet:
Miata ECU motherboard 1996-1997 (NA8 OBD2). Carries the year-specific harness header and the year-independent I/O (wideband, MAP, IAT, USB-C). All engine control is on the daughterboard.

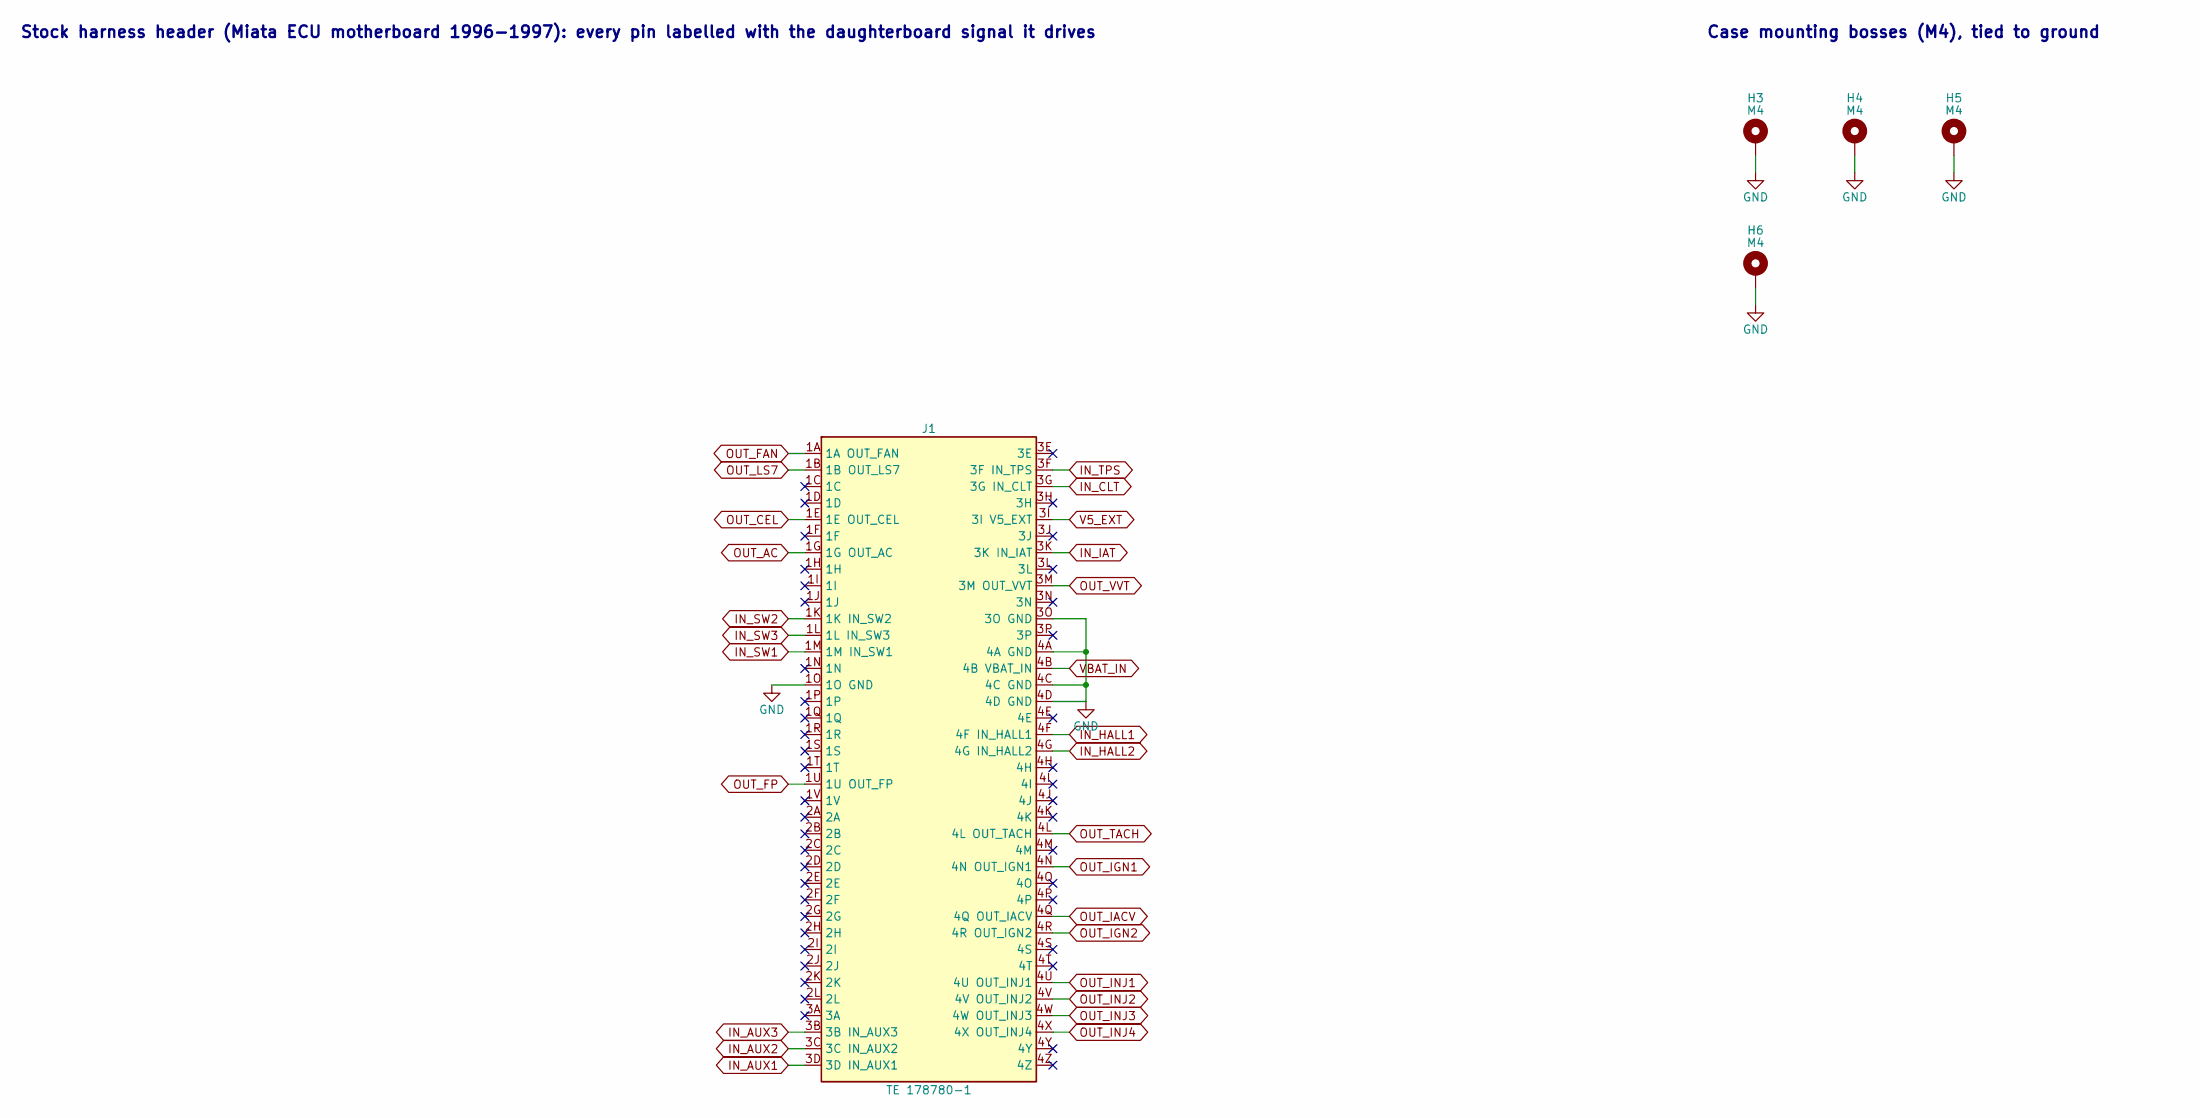
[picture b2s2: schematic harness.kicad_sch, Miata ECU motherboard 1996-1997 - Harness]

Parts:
H3, H4, H5, H6: M4; MountingHole_M4_4.5mm_Pad7
J1: TE 178780-1; TE_178780-1_76P

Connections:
GND: H3.1, H4.1, H5.1, H6.1, J1.1O (1O GND), J1.3O (3O GND), J1.4A (4A GND), J1.4C (4C GND), J1.4D (4D GND); also elsewhere on the board
IN_AUX1: J1.3D (3D IN_AUX1); also elsewhere on the board
IN_AUX2: J1.3C (3C IN_AUX2); also elsewhere on the board
IN_AUX3: J1.3B (3B IN_AUX3); also elsewhere on the board
IN_CLT: J1.3G (3G IN_CLT); also elsewhere on the board
IN_HALL1: J1.4F (4F IN_HALL1); also elsewhere on the board
IN_HALL2: J1.4G (4G IN_HALL2); also elsewhere on the board
IN_IAT: J1.3K (3K IN_IAT); also elsewhere on the board
IN_SW1: J1.1M (1M IN_SW1); also elsewhere on the board
IN_SW2: J1.1K (1K IN_SW2); also elsewhere on the board
IN_SW3: J1.1L (1L IN_SW3); also elsewhere on the board
IN_TPS: J1.3F (3F IN_TPS); also elsewhere on the board
OUT_AC: J1.1G (1G OUT_AC); also elsewhere on the board
OUT_CEL: J1.1E (1E OUT_CEL); also elsewhere on the board
OUT_FAN: J1.1A (1A OUT_FAN); also elsewhere on the board
OUT_FP: J1.1U (1U OUT_FP); also elsewhere on the board
OUT_IACV: J1.4Q (4Q OUT_IACV); also elsewhere on the board
OUT_IGN1: J1.4N (4N OUT_IGN1); also elsewhere on the board
OUT_IGN2: J1.4R (4R OUT_IGN2); also elsewhere on the board
OUT_INJ1: J1.4U (4U OUT_INJ1); also elsewhere on the board
OUT_INJ2: J1.4V (4V OUT_INJ2); also elsewhere on the board
OUT_INJ3: J1.4W (4W OUT_INJ3); also elsewhere on the board
OUT_INJ4: J1.4X (4X OUT_INJ4); also elsewhere on the board
OUT_LS7: J1.1B (1B OUT_LS7); also elsewhere on the board
OUT_TACH: J1.4L (4L OUT_TACH); also elsewhere on the board
OUT_VVT: J1.3M (3M OUT_VVT); also elsewhere on the board
V5_EXT: J1.3I (3I V5_EXT); also elsewhere on the board
VBAT_IN: J1.4B (4B VBAT_IN); also elsewhere on the board

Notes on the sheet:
Stock harness header (Miata ECU motherboard 1996-1997): every pin labelled with the daughterboard signal it drives
Case mounting bosses (M4), tied to ground
